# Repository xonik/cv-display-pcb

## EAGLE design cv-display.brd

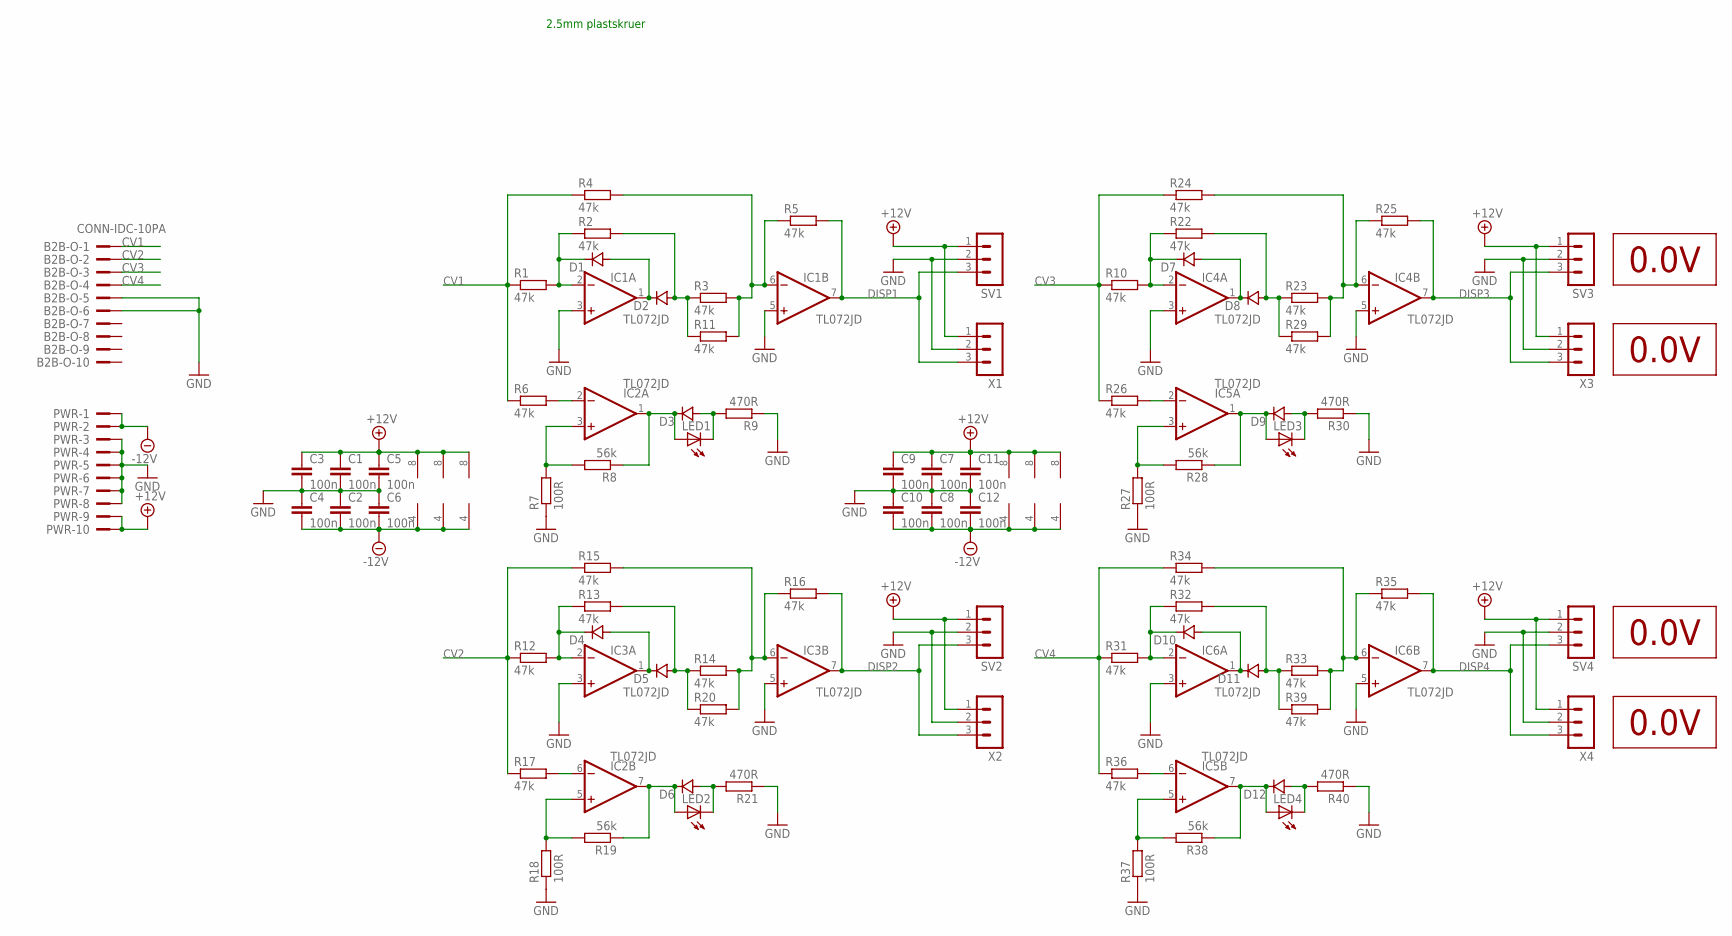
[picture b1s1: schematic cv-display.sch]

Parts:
B2B-O: CONN-IDC-10PA; CONN-IDC10P-A
C1, C2, C3, C4, C5, C6, C7, C8, C9, C10, C11, C12: 100n; C0603
D1, D2, D3, D4, D5, D6, D7, D8, D9, D10, D11, D12: 1N4148SOD323; SOD323J
IC1, IC2, IC3, IC4, IC5, IC6: TL072JD; SO08J
IC7, IC8, IC9, IC10: VOLTMETER
LED1, LED2, LED3, LED4: LED_J2X4; LED2X4-J
PWR: CONN-IDC-10PA; CONN-IDC10P-A
R1, R2, R3, R4, R5, R6, R10, R11, R12, R13, R14, R15, R16, R17, R20, R22, R23, R24, R25, R26, R29, R31, R32, R33, R34, R35, R36, R39: 47k; R0603
R7, R18, R27, R37: 100R; R0603
R8, R19, R28, R38: 56k; R0603
R9, R21, R30, R40: 470R; R0603
SV1, SV2, SV3, SV4: MA03-1JC; MA03-1J
X1, X2, X3, X4: WJ300V-5.0-3P

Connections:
+12V: C1.1, C3.1, C5.1, C7.1, C9.1, C11.1, IC1.8 (V+), IC2.8 (V+), IC3.8 (V+), IC4.8 (V+), IC5.8 (V+), IC6.8 (V+), PWR.9, PWR.10, SV1.1, SV2.1, SV3.1, SV4.1, X1.1, X2.1, X3.1, X4.1
-12V: C2.2, C4.2, C6.2, C8.2, C10.2, C12.2, IC1.4 (V-), IC2.4 (V-), IC3.4 (V-), IC4.4 (V-), IC5.4 (V-), IC6.4 (V-), PWR.1, PWR.2
CV1: B2B-O.1, R1.1, R4.1, R6.1
CV2: B2B-O.2, R12.1, R15.1, R17.1
CV3: B2B-O.3, R10.1, R24.1, R26.1
CV4: B2B-O.4, R31.1, R34.1, R36.1
DISP1: IC1.7 (OUT), R5.2, SV1.3, X1.3
DISP2: IC3.7 (OUT), R16.2, SV2.3, X2.3
DISP3: IC4.7 (OUT), R25.2, SV3.3, X3.3
DISP4: IC6.7 (OUT), R35.2, SV4.3, X4.3
GND: B2B-O.5, B2B-O.6, C1.2, C2.1, C3.2, C4.1, C5.2, C6.1, C7.2, C8.1, C9.2, C10.1, C11.2, C12.1, IC1.3 (+IN), IC1.5 (+IN), IC3.3 (+IN), IC3.5 (+IN), IC4.3 (+IN), IC4.5 (+IN), IC6.3 (+IN), IC6.5 (+IN), PWR.3, PWR.4, PWR.5, PWR.6, PWR.7, PWR.8, R7.1, R9.1, R18.1, R21.1, R27.1, R30.1, R37.1, R40.1, SV1.2, SV2.2, SV3.2, SV4.2, X1.2, X2.2, X3.2, X4.2
unnamed: D1.1 (C), IC1.2 (-IN), R1.2, R2.1
unnamed: D1.2 (A), D2.1 (C), IC1.1 (OUT)
unnamed: IC2.3 (+IN), R7.2, R8.2
unnamed: D2.2 (A), R2.2, R3.1, R11.1
unnamed: D7.1 (C), IC4.2 (-IN), R10.2, R22.1
unnamed: D3.1 (C), IC2.1 (OUT), LED1.ANODE (A), R8.1
unnamed: D7.2 (A), D8.1 (C), IC4.1 (OUT)
unnamed: IC1.6 (-IN), R3.2, R4.2, R5.1, R11.2
unnamed: IC2.2 (-IN), R6.2
unnamed: D8.2 (A), R22.2, R23.1, R29.1
unnamed: IC4.6 (-IN), R23.2, R24.2, R25.1, R29.2
unnamed: D3.2 (A), LED1.CATHODE (C), R9.2
unnamed: D4.1 (C), IC3.2 (-IN), R12.2, R13.1
unnamed: D4.2 (A), D5.1 (C), IC3.1 (OUT)
unnamed: D5.2 (A), R13.2, R14.1, R20.1
unnamed: IC3.6 (-IN), R14.2, R15.2, R16.1, R20.2
unnamed: IC2.6 (-IN), R17.2
unnamed: IC2.5 (+IN), R18.2, R19.2
unnamed: D6.1 (C), IC2.7 (OUT), LED2.ANODE (A), R19.1
unnamed: D6.2 (A), LED2.CATHODE (C), R21.2
unnamed: IC5.2 (-IN), R26.2
unnamed: IC5.3 (+IN), R27.2, R28.2
unnamed: D9.1 (C), IC5.1 (OUT), LED3.ANODE (A), R28.1
unnamed: D9.2 (A), LED3.CATHODE (C), R30.2
unnamed: D10.1 (C), IC6.2 (-IN), R31.2, R32.1
unnamed: D10.2 (A), D11.1 (C), IC6.1 (OUT)
unnamed: D11.2 (A), R32.2, R33.1, R39.1
unnamed: IC6.6 (-IN), R33.2, R34.2, R35.1, R39.2
unnamed: IC5.6 (-IN), R36.2
unnamed: IC5.5 (+IN), R37.2, R38.2
unnamed: D12.1 (C), IC5.7 (OUT), LED4.ANODE (A), R38.1
unnamed: D12.2 (A), LED4.CATHODE (C), R40.2

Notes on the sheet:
2.5mm plastskruer

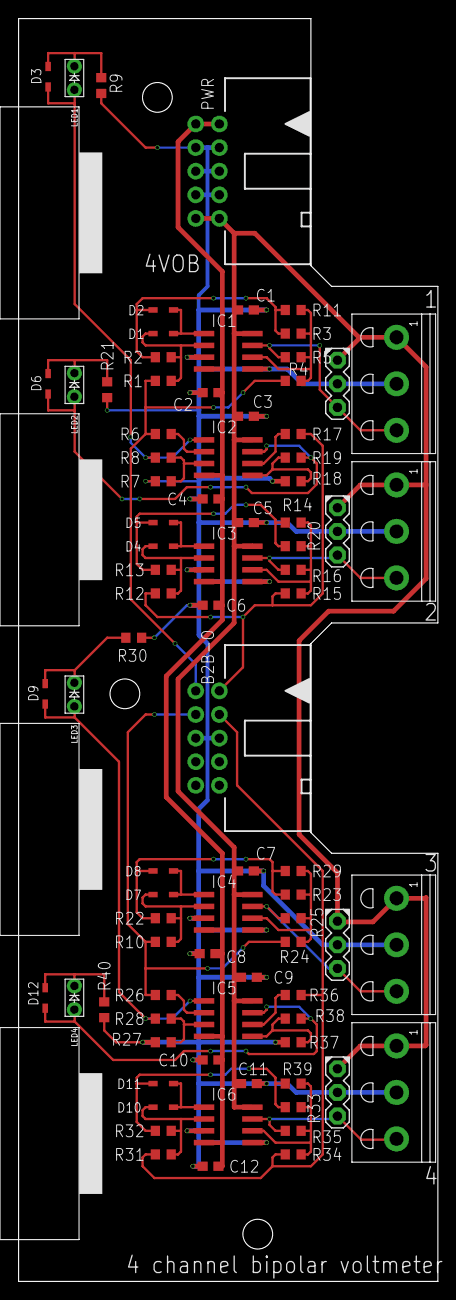
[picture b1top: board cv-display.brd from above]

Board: 2 copper layers, 45.1 x 135.8 mm, 88 parts (0 on the bottom side), 43 nets.

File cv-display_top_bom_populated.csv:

Comment,Designator,Footprint,LCSC Part #
1N4148SOD323,D1 D2 D3 D4 D5 D6 D7 D8 D9 D10 D11 D12,SOD323J,C2128
47k,R1 R2 R3 R4 R5 R6 R10 R11 R12 R13 R14 R15 R16 R17 R20 R22 R23 R24 R25 R26 R29 R31 R32 R33 R34 R35 R36 R39,R0603,C25819
56k,R8 R19 R28 R38,R0603,C23206
100R,R7 R18 R27 R37,R0603,C22775
100n,C1 C2 C3 C4 C5 C6 C7 C8 C9 C10 C11 C12,C0603,C14663
470R,R9 R21 R30 R40,R0603,C23179
CONN-IDC-10PA,B2B-O PWR,CONN-IDC10P-A,C132437
TL072JD,IC1 IC2 IC3 IC4 IC5 IC6,SO08,C6961
WJ300V-5.0-3P,X1 X2 X3 X4,WJ300V-5.0-3P,C8483

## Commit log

2023-07-20 Initial commit, rectifier and sign circuit ready
2023-07-21 Tested circuit, only missing screw terminals
2023-07-24 Traced almost everything
2023-07-24 No airwires, just led placements left
2023-08-06 Fixed leds and display sizes
2023-08-06 Wrong led positions
2023-12-09 Sent to production
2023-12-09 Moved sent to prod
